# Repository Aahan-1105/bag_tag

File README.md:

# bag_tag
Created for the half-life program by Hack Club, bag_tag is an accessory inspired by content seen online and features a relatively large oled screen and a 110 maH LiPO cell alongside 3 low profile switches for some basic control. I aim to have the device easily configurable over BLE to allow for easy addition of your favorite memes and animations to the display! It'll also have an info page for owner info and whatever you want on there!

## Images

Completed Schematic

Finished PCB with Traces

Fill Zone

PCB 3D view

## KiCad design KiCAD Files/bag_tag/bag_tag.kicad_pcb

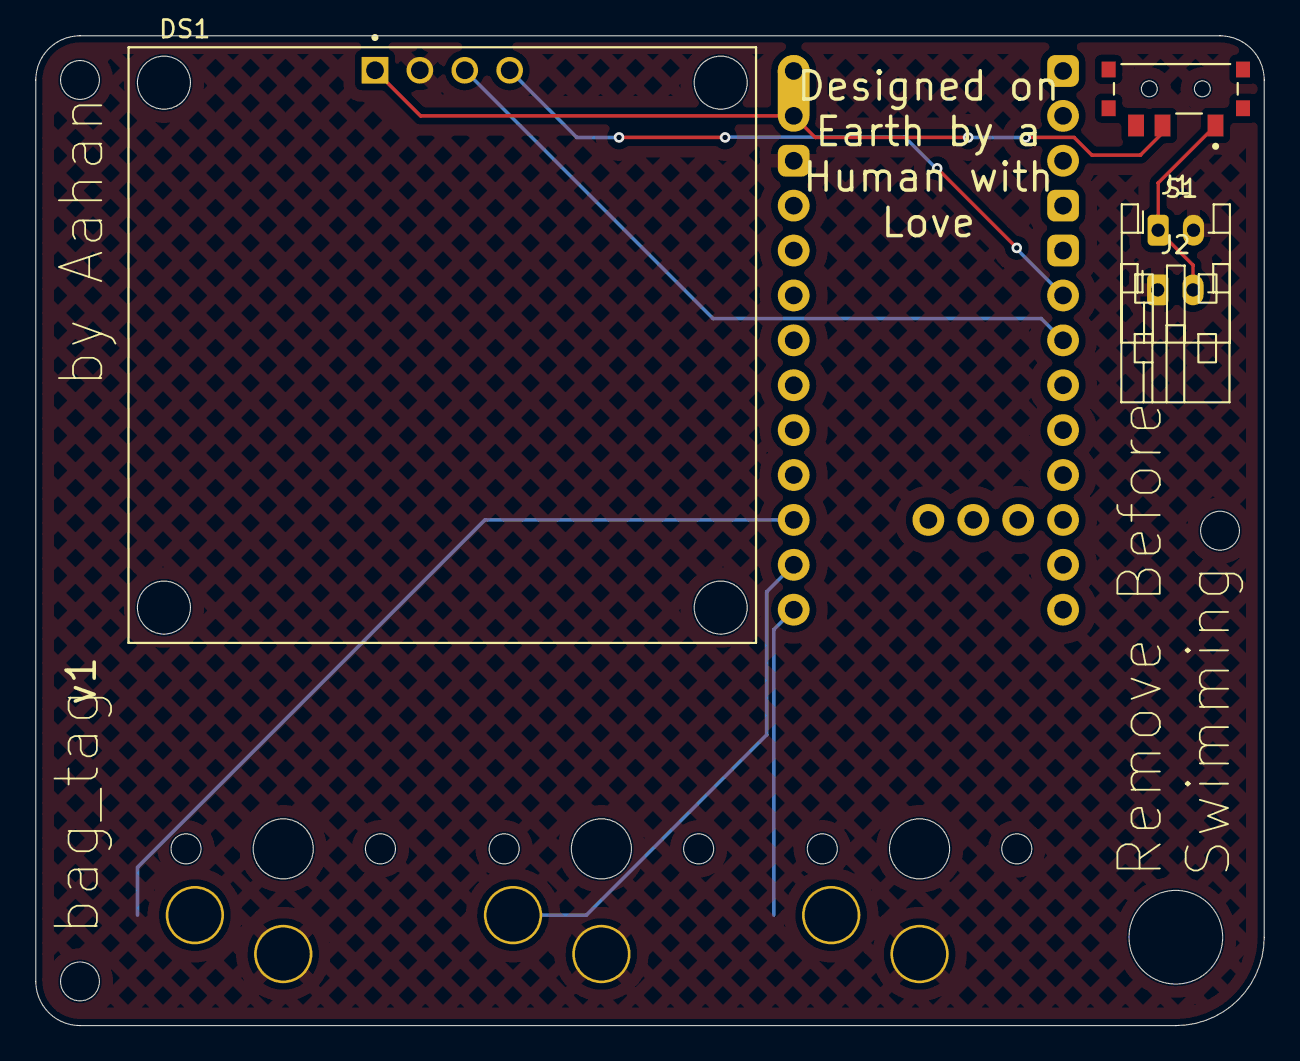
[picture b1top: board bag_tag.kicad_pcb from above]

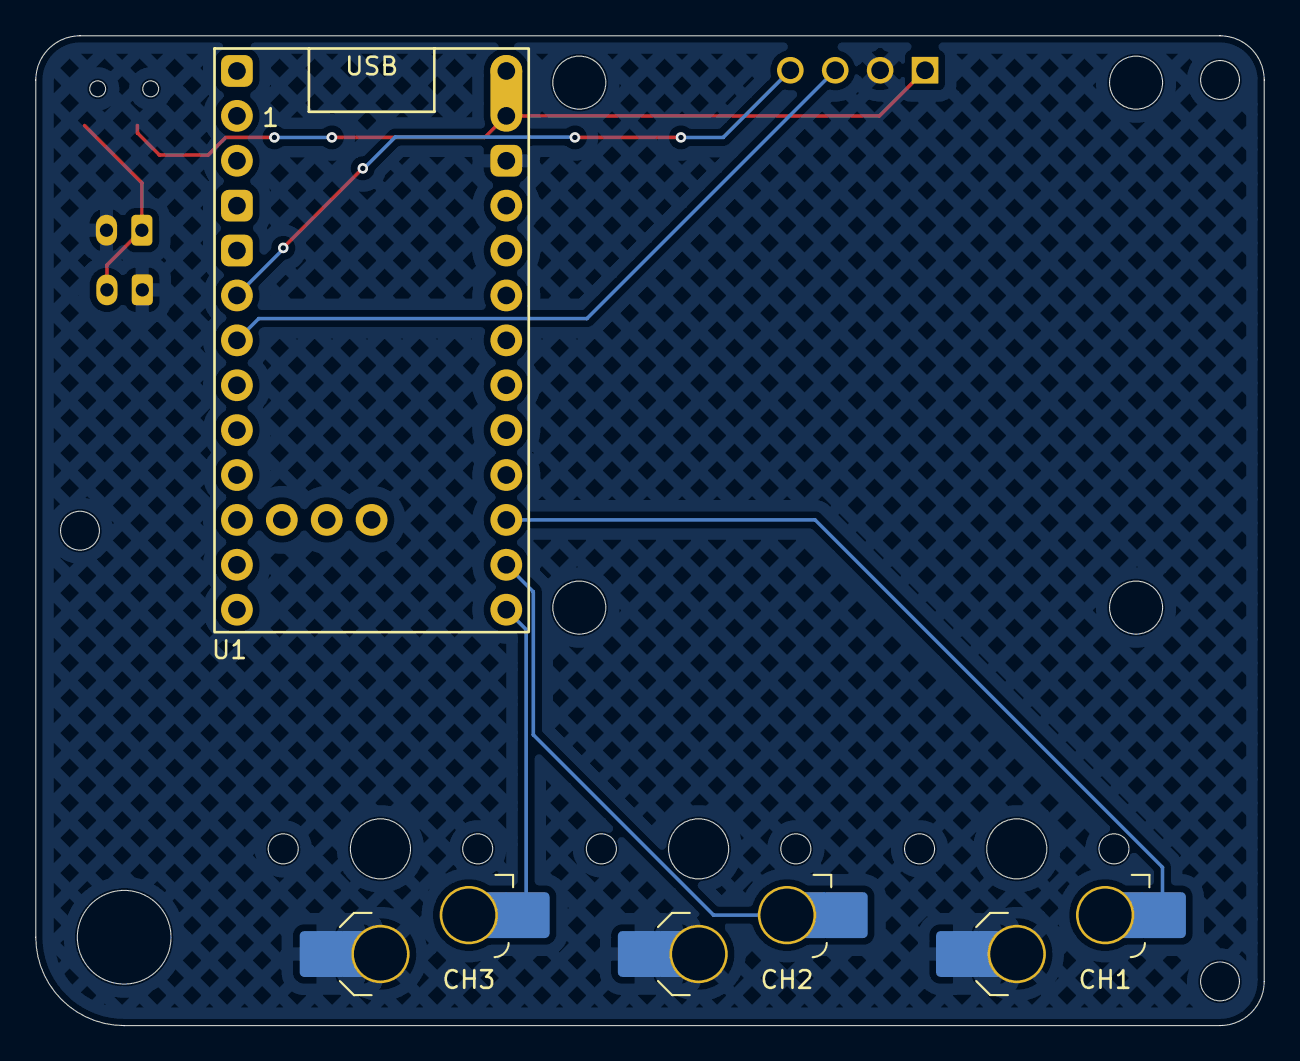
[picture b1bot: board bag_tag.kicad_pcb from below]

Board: 2 copper layers, 69.5 x 56.0 mm, 8 parts (4 on the bottom side), 8 nets.

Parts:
CH1, CH2, CH3: choc_v1_SW_HS; SW_choc_v1_HS_CPG135001S30_1u
DS1: OLED_128X64_1.3_I2C; LCD_OLED_128X64_1.3_I2C
J1, J2: Conn_01x02_Socket; JST_PH_S2B-PH-K_1x02_P2.00mm_Horizontal
S1: MSK12C02; SW_MSK12C02
U1: nice_nano; nice_nano_AH_USBup

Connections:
+BATT: J1.1, J2.2, S1.1
/SCK: DS1.3 (SCK), U1.6 (P0.20)
/SDA: DS1.4 (SDA), U1.5 (P0.17)
/SW1: CH1.1, U1.22 (P1.11-LF)
/SW2: CH2.1, U1.23 (P0.10-LF)
/SW3: CH3.1, U1.24 (P0.09-LF)
GND: CH1.2, CH2.2, CH3.2, DS1.2 (GND), J1.2, J2.1, U1.14 (GND)
VCC: DS1.1 (VDD), S1.2, U1.13 (BAT+), U1.29 (BAT+)
